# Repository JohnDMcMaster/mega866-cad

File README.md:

# mega866
Aggregate four TL866s into a single ZSM host.

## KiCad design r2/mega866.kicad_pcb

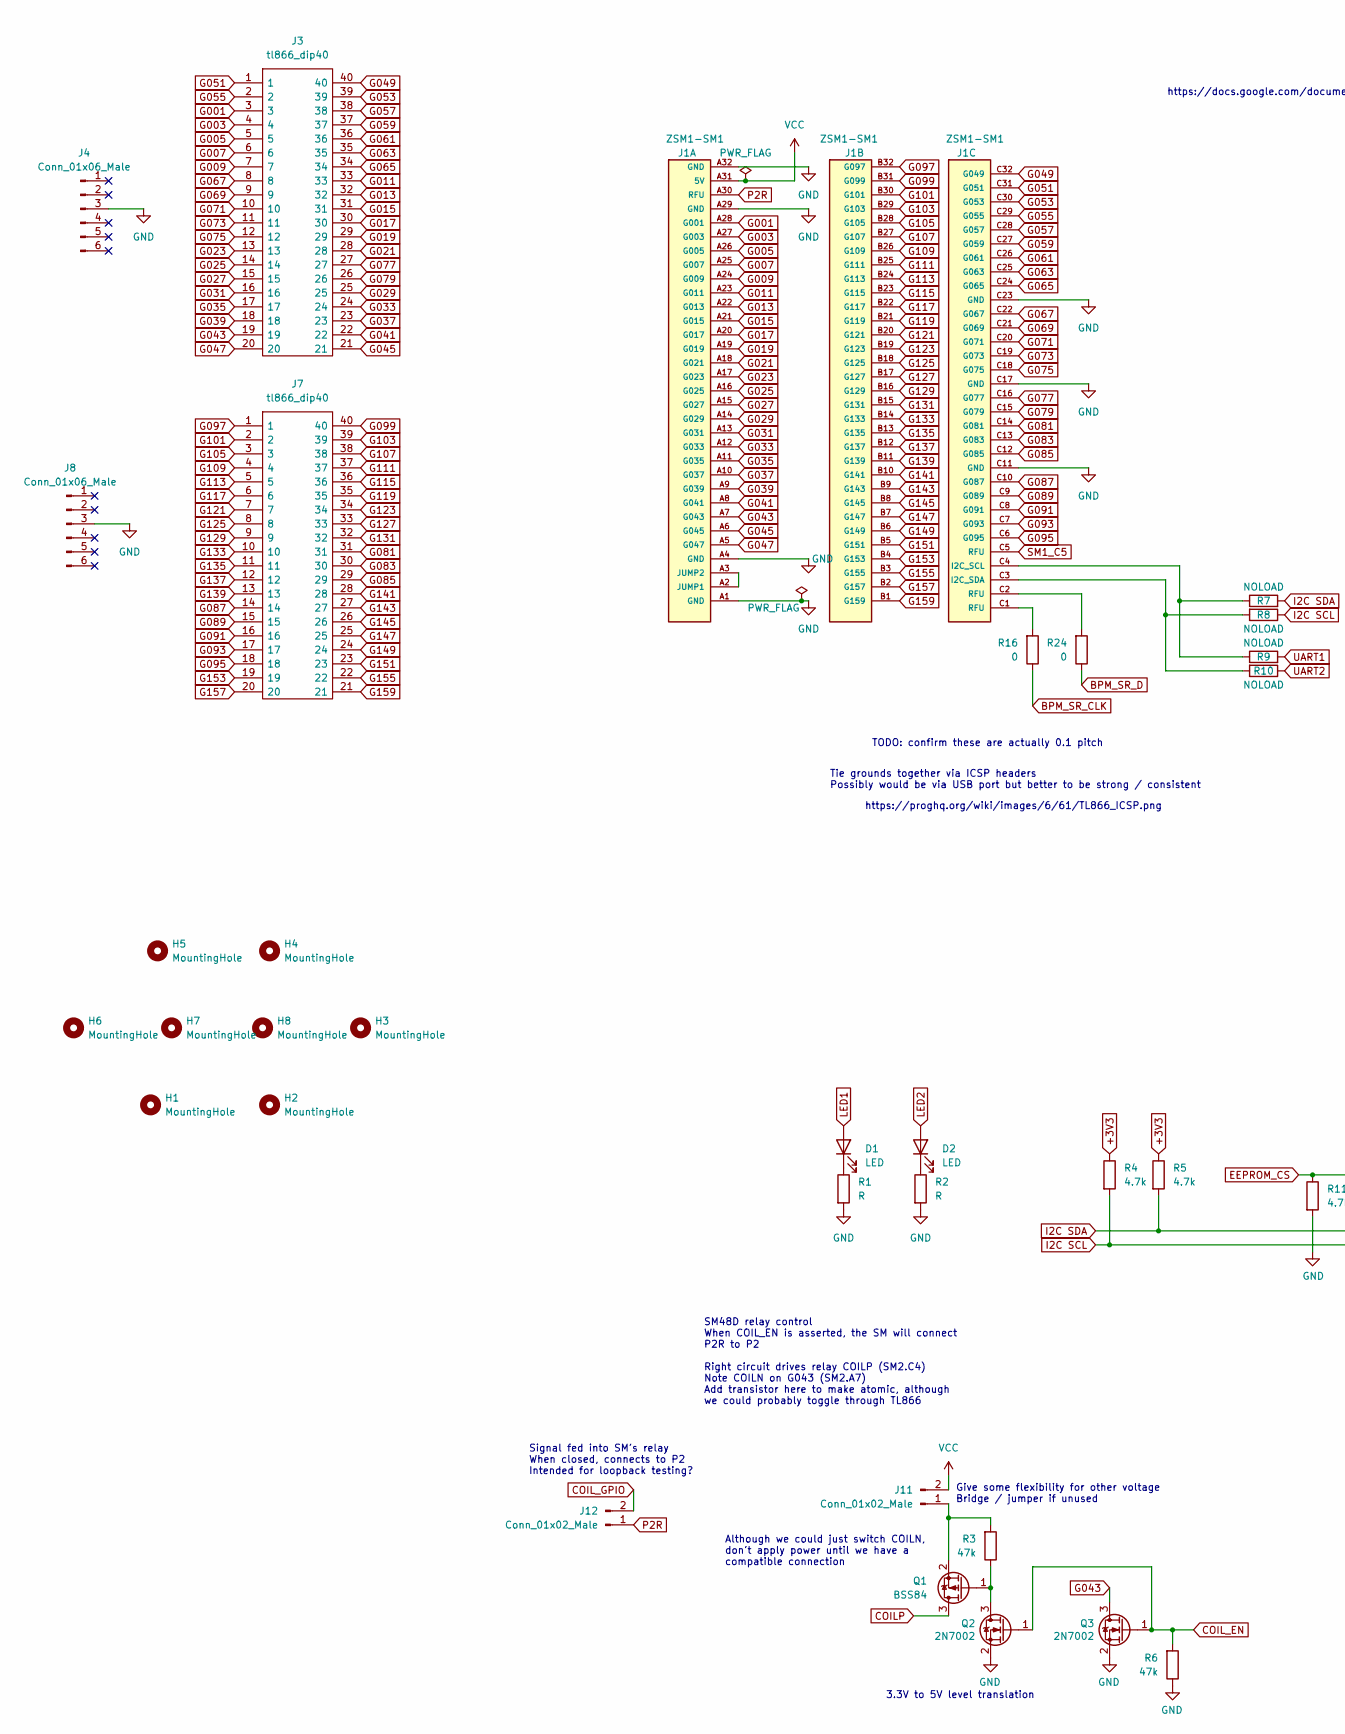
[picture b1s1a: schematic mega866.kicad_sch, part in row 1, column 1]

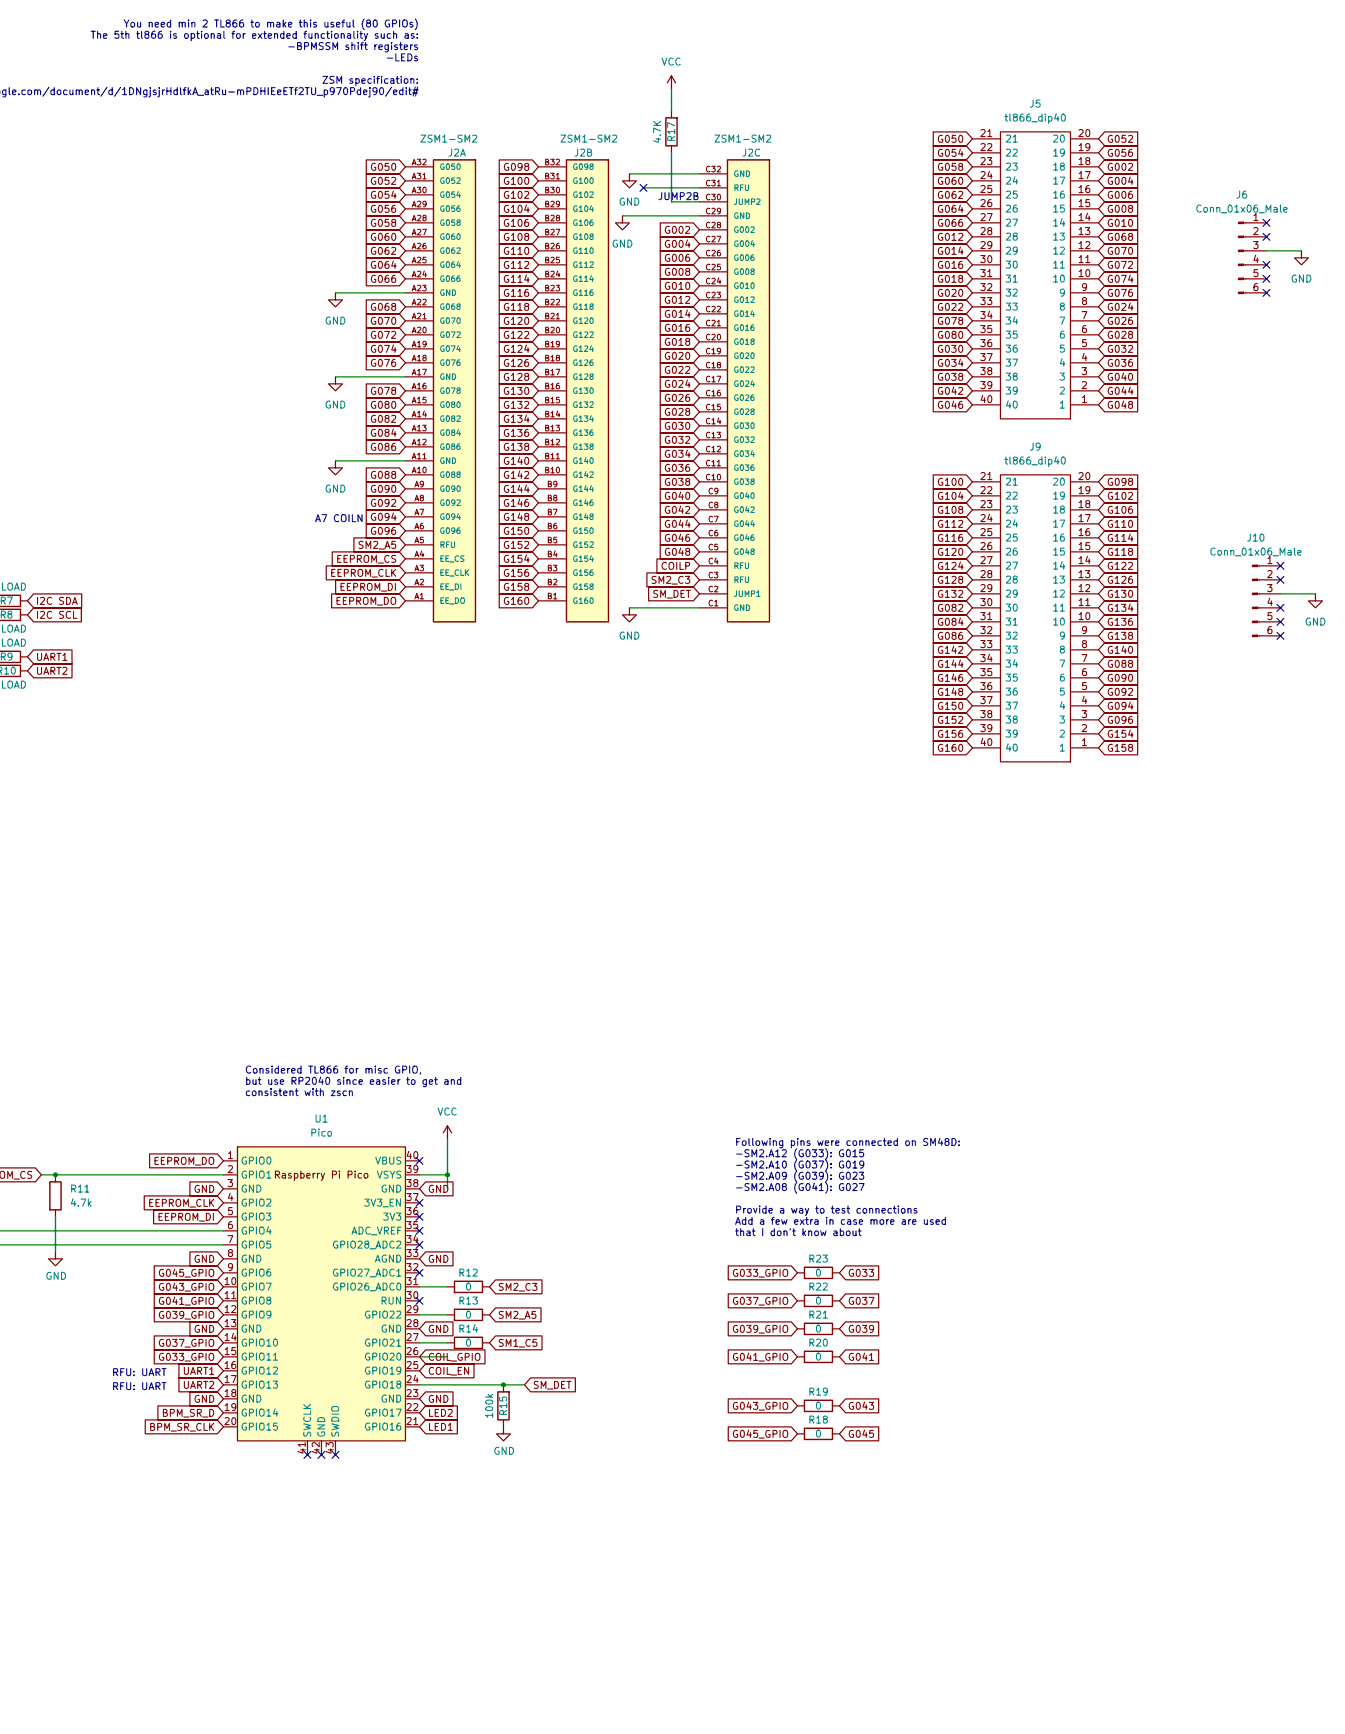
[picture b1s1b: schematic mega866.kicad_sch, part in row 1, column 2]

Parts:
D1, D2: LED; LED_0603_1608Metric
H1, H2, H3, H4, H5, H6, H7, H8: MountingHole; MountingHole_4.3mm_M4_DIN965
J1: ZSM1-SM1; 5650470-5; PARTREV O1
J2: ZSM1-SM2; 5650470-5; PARTREV O1
J3, J5, J7, J9: tl866_dip40; tl866
J4, J6, J8, J10: Conn_01x06_Male; PinHeader_1x06_P2.54mm_Vertical
J11, J12: Conn_01x02_Male; PinHeader_1x02_P2.54mm_Vertical
Q1: BSS84; SOT-23
Q2, Q3: 2N7002; SOT-23
R1, R2: R; R_0603_1608Metric
R3, R6: 47k; R_0603_1608Metric
R4, R5, R11: 4.7k; R_0603_1608Metric
R7, R8, R9, R10: NOLOAD; R_0603_1608Metric
R12, R13, R14, R16, R18, R19, R20, R21, R22, R23, R24: 0; R_0603_1608Metric
R15: 100k; R_0603_1608Metric
R17: 4.7K; R_0603_1608Metric
U1: Pico; RPi_Pico_SMD_TH

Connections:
+3V3: R4.1, R5.1
BPM_SR_CLK: R16.1, U1.20 (GPIO15)
BPM_SR_D: R24.1, U1.19 (GPIO14)
COILP: J2.C4 (RFU), Q1.3 (D)
COIL_EN: Q2.1 (G), Q3.1 (G), R6.2, U1.25 (GPIO19)
COIL_GPIO: J12.2, U1.26 (GPIO20)
EEPROM_CLK: J2.A3 (EE_CLK), U1.4 (GPIO2)
EEPROM_CS: J2.A4 (EE_CS), R11.1, U1.2 (GPIO1)
EEPROM_DI: J2.A2 (EE_DI), U1.5 (GPIO3)
EEPROM_DO: J2.A1 (EE_DO), U1.1 (GPIO0)
G001: J1.A28 (G001), J3.3
G002: J2.C28 (G002), J5.18
G003: J1.A27 (G003), J3.4
G004: J2.C27 (G004), J5.17
G005: J1.A26 (G005), J3.5
G006: J2.C26 (G006), J5.16
G007: J1.A25 (G007), J3.6
G008: J2.C25 (G008), J5.15
G009: J1.A24 (G009), J3.7
G010: J2.C24 (G010), J5.14
G011: J1.A23 (G011), J3.33
G012: J2.C23 (G012), J5.28
G013: J1.A22 (G013), J3.32
G014: J2.C22 (G014), J5.29
G015: J1.A21 (G015), J3.31
G016: J2.C21 (G016), J5.30
G017: J1.A20 (G017), J3.30
G018: J2.C20 (G018), J5.31
G019: J1.A19 (G019), J3.29
G020: J2.C19 (G020), J5.32
G021: J1.A18 (G021), J3.28
G022: J2.C18 (G022), J5.33
G023: J1.A17 (G023), J3.13
G024: J2.C17 (G024), J5.8
G025: J1.A16 (G025), J3.14
G026: J2.C16 (G026), J5.7
G027: J1.A15 (G027), J3.15
G028: J2.C15 (G028), J5.6
G029: J1.A14 (G029), J3.25
G030: J2.C14 (G030), J5.36
G031: J1.A13 (G031), J3.16
G032: J2.C13 (G032), J5.5
G033: J1.A12 (G033), J3.24, R23.1
G033_GPIO: R23.2, U1.15 (GPIO11)
G034: J2.C12 (G034), J5.37
G035: J1.A11 (G035), J3.17
G036: J2.C11 (G036), J5.4
G037: J1.A10 (G037), J3.23, R22.1
G037_GPIO: R22.2, U1.14 (GPIO10)
G038: J2.C10 (G038), J5.38
G039: J1.A9 (G039), J3.18, R21.1
G039_GPIO: R21.2, U1.12 (GPIO9)
G040: J2.C9 (G040), J5.3
G041: J1.A8 (G041), J3.22, R20.1
G041_GPIO: R20.2, U1.11 (GPIO8)
G042: J2.C8 (G042), J5.39
G043: J1.A7 (G043), J3.19, Q3.3 (D), R19.1
G043_GPIO: R19.2, U1.10 (GPIO7)
G044: J2.C7 (G044), J5.2
G045: J1.A6 (G045), J3.21, R18.1
G045_GPIO: R18.2, U1.9 (GPIO6)
G046: J2.C6 (G046), J5.40
G047: J1.A5 (G047), J3.20
G048: J2.C5 (G048), J5.1
G049: J1.C32 (G049), J3.40
G050: J2.A32 (G050), J5.21
G051: J1.C31 (G051), J3.1
G052: J2.A31 (G052), J5.20
G053: J1.C30 (G053), J3.39
G054: J2.A30 (G054), J5.22
G055: J1.C29 (G055), J3.2
G056: J2.A29 (G056), J5.19
G057: J1.C28 (G057), J3.38
G058: J2.A28 (G058), J5.23
G059: J1.C27 (G059), J3.37
G060: J2.A27 (G060), J5.24
G061: J1.C26 (G061), J3.36
G062: J2.A26 (G062), J5.25
G063: J1.C25 (G063), J3.35
G064: J2.A25 (G064), J5.26
G065: J1.C24 (G065), J3.34
G066: J2.A24 (G066), J5.27
G067: J1.C22 (G067), J3.8
G068: J2.A22 (G068), J5.13
G069: J1.C21 (G069), J3.9
G070: J2.A21 (G070), J5.12
G071: J1.C20 (G071), J3.10
G072: J2.A20 (G072), J5.11
G073: J1.C19 (G073), J3.11
G074: J2.A19 (G074), J5.10
G075: J1.C18 (G075), J3.12
G076: J2.A18 (G076), J5.9
G077: J1.C16 (G077), J3.27
G078: J2.A16 (G078), J5.34
G079: J1.C15 (G079), J3.26
G080: J2.A15 (G080), J5.35
G081: J1.C14 (G081), J7.31
G082: J2.A14 (G082), J9.30
G083: J1.C13 (G083), J7.30
G084: J2.A13 (G084), J9.31
G085: J1.C12 (G085), J7.29
G086: J2.A12 (G086), J9.32
G087: J1.C10 (G087), J7.14
G088: J2.A10 (G088), J9.7
G089: J1.C9 (G089), J7.15
G090: J2.A9 (G090), J9.6
G091: J1.C8 (G091), J7.16
G092: J2.A8 (G092), J9.5
G093: J1.C7 (G093), J7.17
G094: J2.A7 (G094), J9.4
G095: J1.C6 (G095), J7.18
G096: J2.A6 (G096), J9.3
G097: J1.B32 (G097), J7.1
G098: J2.B32 (G098), J9.20
G099: J1.B31 (G099), J7.40
G100: J2.B31 (G100), J9.21
G101: J1.B30 (G101), J7.2
G102: J2.B30 (G102), J9.19
G103: J1.B29 (G103), J7.39
G104: J2.B29 (G104), J9.22
G105: J1.B28 (G105), J7.3
G106: J2.B28 (G106), J9.18
G107: J1.B27 (G107), J7.38
G108: J2.B27 (G108), J9.23
G109: J1.B26 (G109), J7.4
G110: J2.B26 (G110), J9.17
G111: J1.B25 (G111), J7.37
G112: J2.B25 (G112), J9.24
G113: J1.B24 (G113), J7.5
G114: J2.B24 (G114), J9.16
G115: J1.B23 (G115), J7.36
G116: J2.B23 (G116), J9.25
G117: J1.B22 (G117), J7.6
G118: J2.B22 (G118), J9.15
G119: J1.B21 (G119), J7.35
G120: J2.B21 (G120), J9.26
G121: J1.B20 (G121), J7.7
G122: J2.B20 (G122), J9.14
G123: J1.B19 (G123), J7.34
G124: J2.B19 (G124), J9.27
G125: J1.B18 (G125), J7.8
G126: J2.B18 (G126), J9.13
G127: J1.B17 (G127), J7.33
G128: J2.B17 (G128), J9.28
G129: J1.B16 (G129), J7.9
G130: J2.B16 (G130), J9.12
G131: J1.B15 (G131), J7.32
G132: J2.B15 (G132), J9.29
G133: J1.B14 (G133), J7.10
G134: J2.B14 (G134), J9.11
G135: J1.B13 (G135), J7.11
G136: J2.B13 (G136), J9.10
G137: J1.B12 (G137), J7.12
G138: J2.B12 (G138), J9.9
G139: J1.B11 (G139), J7.13
G140: J2.B11 (G140), J9.8
G141: J1.B10 (G141), J7.28
G142: J2.B10 (G142), J9.33
G143: J1.B9 (G143), J7.27
G144: J2.B9 (G144), J9.34
G145: J1.B8 (G145), J7.26
G146: J2.B8 (G146), J9.35
G147: J1.B7 (G147), J7.25
G148: J2.B7 (G148), J9.36
G149: J1.B6 (G149), J7.24
G150: J2.B6 (G150), J9.37
G151: J1.B5 (G151), J7.23
G152: J2.B5 (G152), J9.38
G153: J1.B4 (G153), J7.19
G154: J2.B4 (G154), J9.2
G155: J1.B3 (G155), J7.22
G156: J2.B3 (G156), J9.39
G157: J1.B2 (G157), J7.20
G158: J2.B2 (G158), J9.1
G159: J1.B1 (G159), J7.21
G160: J2.B1 (G160), J9.40
GND: J1.A1 (GND), J1.A4 (GND), J1.A29 (GND), J1.A32 (GND), J1.C11 (GND), J1.C17 (GND), J1.C23 (GND), J2.A11 (GND), J2.A17 (GND), J2.A23 (GND), J2.C1 (GND), J2.C29 (GND), J2.C32 (GND), J4.3, J6.3, J8.3, J10.3, Q2.2 (S), Q3.2 (S), R1.2, R2.2, R6.1, R11.2, R15.1, U1.3 (GND), U1.8 (GND), U1.13 (GND), U1.18 (GND), U1.23 (GND), U1.28 (GND), U1.33 (AGND), U1.38 (GND)
I2C SCL: R4.2, R8.1, U1.7 (GPIO5)
I2C SDA: R5.2, R7.2, U1.6 (GPIO4)
LED1: D1.2 (A), U1.21 (GPIO16)
LED2: D2.2 (A), U1.22 (GPIO17)
unnamed: D1.1 (K), R1.1
unnamed: D2.1 (K), R2.1
unnamed: J1.A2 (JUMP1), J1.A3 (JUMP2)
unnamed: J1.C1 (RFU), R16.2
unnamed: J1.C2 (RFU), R24.2
unnamed: J1.C3 (I2C_SDA), R8.2, R10.2
unnamed: J1.C4 (I2C_SCL), R7.1, R9.1
unnamed: J2.C30 (JUMP2), R17.1
unnamed: J11.1, Q1.2 (S), R3.2
unnamed: Q1.1 (G), Q2.3 (D), R3.1
unnamed: R12.2, U1.31 (GPIO26_ADC0)
unnamed: R13.2, U1.29 (GPIO22)
unnamed: R14.2, U1.27 (GPIO21)
P2R: J1.A30 (RFU), J12.1
SM1_C5: J1.C5 (RFU), R14.1
SM2_A5: J2.A5 (RFU), R13.1
SM2_C3: J2.C3 (RFU), R12.1
SM_DET: J2.C2 (JUMP1), R15.2, U1.24 (GPIO18)
UART1: R9.2, U1.16 (GPIO12)
UART2: R10.1, U1.17 (GPIO13)
VCC: J1.A31 (5V), J11.2, R17.2, U1.39 (VSYS)

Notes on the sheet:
Following pins were connected on SM48D: -SM2.A12 (G033): G015 -SM2.A10 (G037): G019 -SM2.A09 (G039): G023 -SM2.A08 (G041): G027 Provide a way to test connections Add a few extra in case more are used that I don't know about
RFU: UART
3.3V to 5V level translation
Considered TL866 for misc GPIO, but use RP2040 since easier to get and consistent with zscn
Tie grounds together via ICSP headers Possibly would be via USB port but better to be strong / consistent
TODO: confirm these are actually 0.1 pitch
JUMP2B
A7 COILN
Give some flexibility for other voltage Bridge / jumper if unused
SM48D relay control When COIL_EN is asserted, the SM will connect P2R to P2 Right circuit drives relay COILP (SM2.C4) Note COILN on G043 (SM2.A7) Add transistor here to make atomic, although we could probably toggle through TL866
Signal fed into SM's relay When closed, connects to P2 Intended for loopback testing?
Although we could just switch COILN, don't apply power until we have a compatible connection
https://proghq.org/wiki/images/6/61/TL866_ICSP.png
You need min 2 TL866 to make this useful (80 GPIOs) The 5th tl866 is optional for extended functionality such as: -BPMSSM shift registers -LEDs ZSM specification: https://docs.google.com/document/d/1DNgjsjrHdlfkA_atRu-mPDHIEeETf2TU_p970Pdej90/edit#

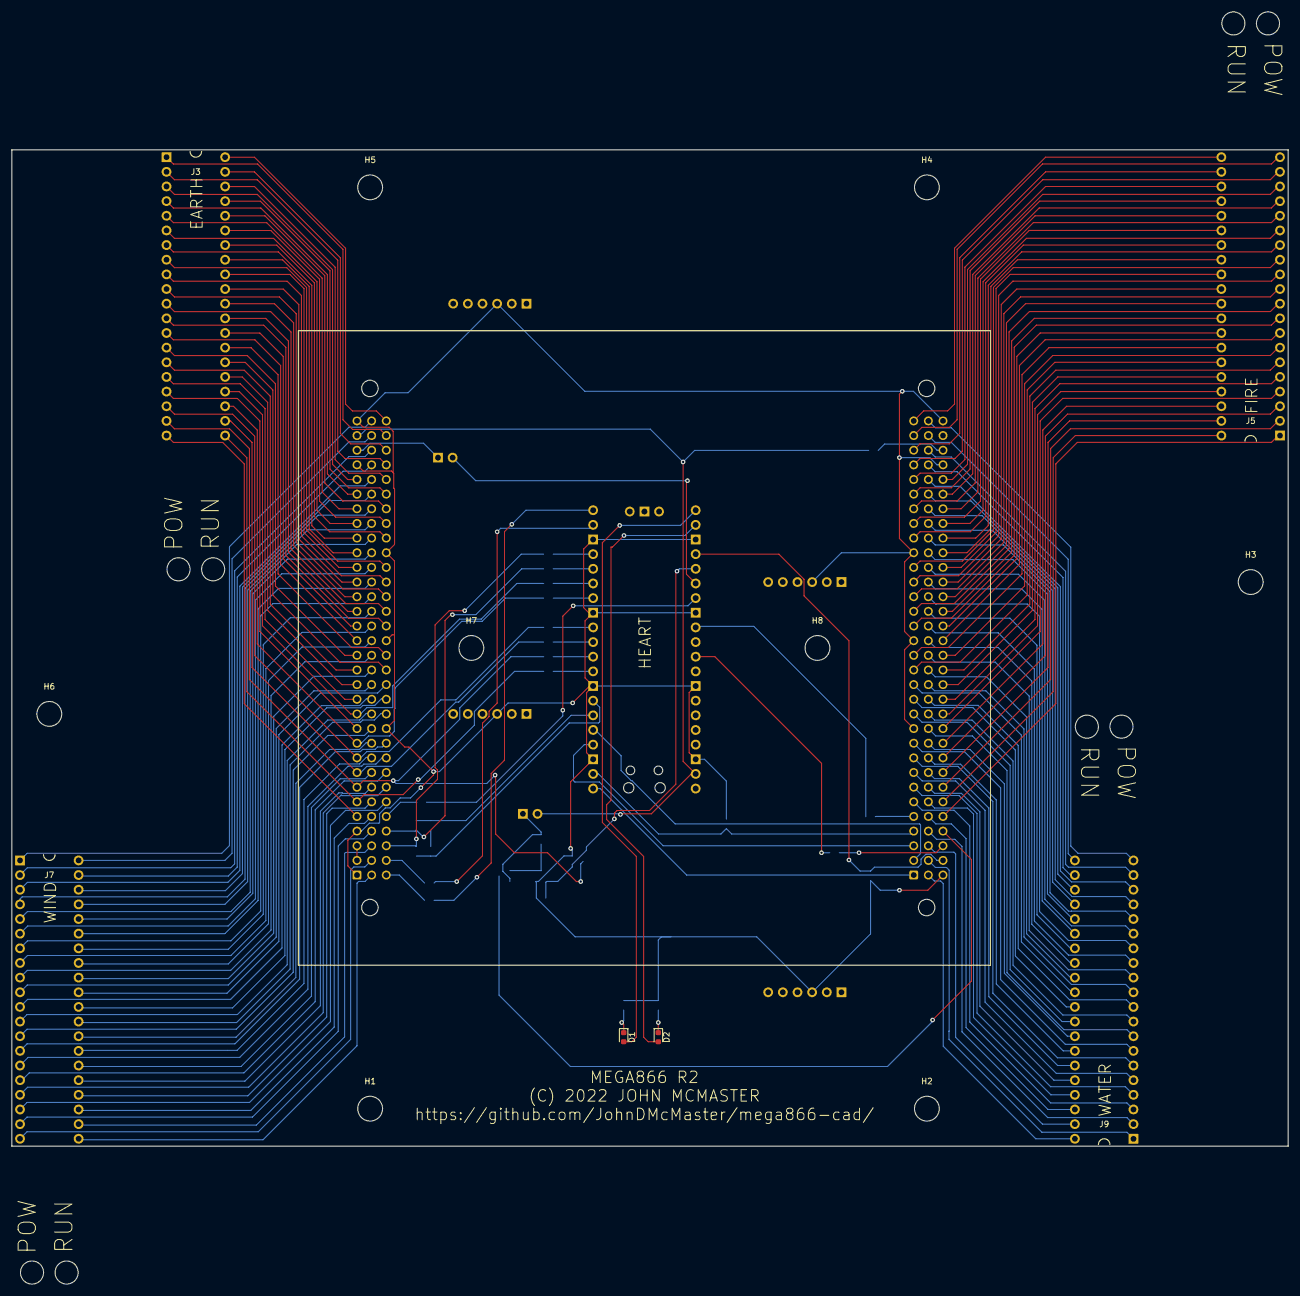
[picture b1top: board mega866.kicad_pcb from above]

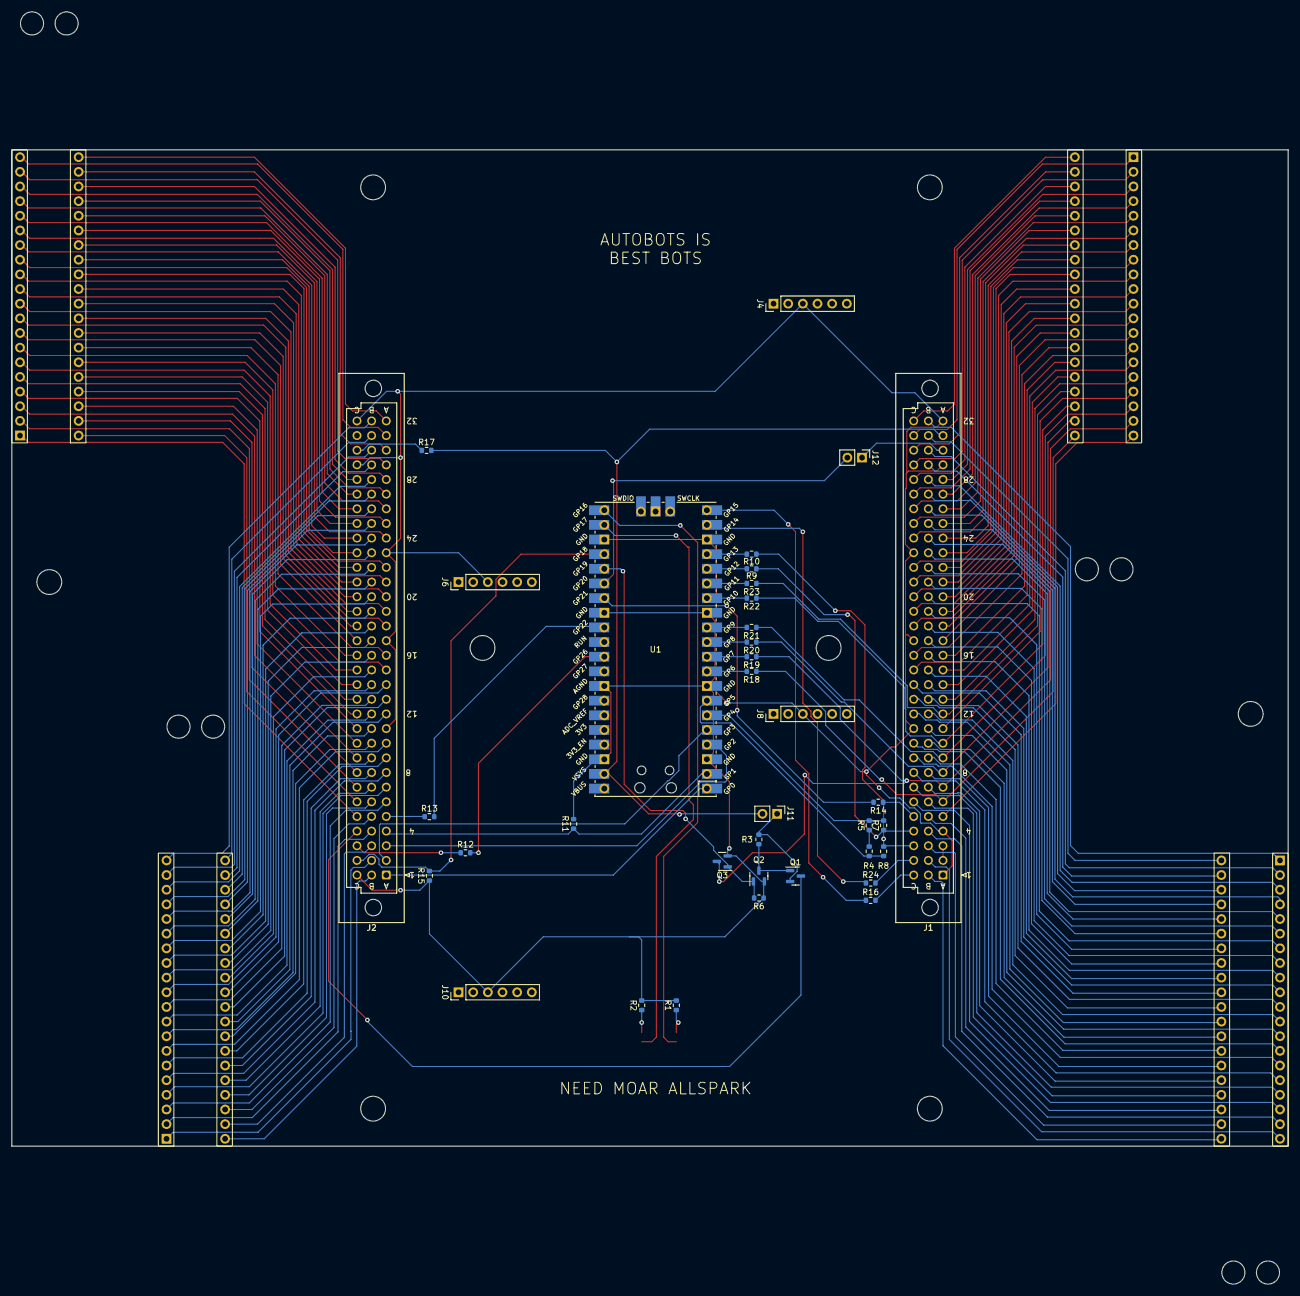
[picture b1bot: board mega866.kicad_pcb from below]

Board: 2 copper layers, 221.3 x 172.7 mm, 50 parts (36 on the bottom side), 202 nets.

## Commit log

2022-10-07 schem PoC
2022-10-09 schematic draft
2022-10-09 fix erc errors
2022-10-09 cleaner drc / fix errors
2022-10-14 reassign pins for easier routing
2022-10-14 release candidate
2022-10-14 tweaks
2022-10-14 releasing
2022-10-14 center LEDs better
2022-10-14 r2: add mounting holes, fix led spacing
2022-10-14 r2 sync
2023-03-10 Fix README wording

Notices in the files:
r2/mega866.kicad_pcb:
(C) 2022 JOHN MCMASTER
